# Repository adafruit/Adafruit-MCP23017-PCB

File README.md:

## Adafruit MCP23017 I2C GPIO Expander Breakout - STEMMA QT / QWIIC PCB

<a href="http://www.adafruit.com/products/5346"><br/>
Click here to purchase one from the Adafruit shop</a>

PCB files for the Adafruit MCP23017 I2C GPIO Expander Breakout - STEMMA QT / QWIIC. 

Format is EagleCAD schematic and board layout
* https://www.adafruit.com/product/5346

### Description

We’ve gotten a lot of requests for a MCP23017 breakout and we’ve always sorta been like “ehh why not just use the DIP chip?” but with STEMMA QT we could see the use case for a plug and play version that comes with all the passives on board. This Adafruit MCP23017 I2C GPIO Expander Breakout has 16 GPIO with matching ground pad.

We particularly like the '17 as an expander for it's simple no-nonsense capability. It runs happily from 3V or 5V logic and power. Each GPIO can be an output driving up to 25mA, so LEDs are no problem. Or, each can be an input, with optional pullup. There are two IRQ pins that are configurable for what inputs to keep track of so no I2C bus polling is required. With 3 address pins, you can have up to 8 on a single bus for a total of 8 x 16 = 128 GPIO all on one I2C bus!

We've got solid Arduino and CircuitPython libraries with examples, all ready for this chip. But even if you are using some other platform, the MCP23017 is so classic, you'll likely be able to find example code.

Comes with two sticks of header so you can use it in a breadboard, with some soldering. You can also free-wire buttons by connecting one side to the GPIO (set as input with pullup) and the other side to a ground pad.

To get you going fast, we spun up a custom-made PCB in the STEMMA QT form factor, making it easy to interface with. The STEMMA QT connectors on either side are compatible with the SparkFun Qwiic I2C connectors. This allows you to make solderless connections between your development board and the MCP23017 or to chain it with a wide range of other sensors and accessories using a compatible cable.

### License

Adafruit invests time and resources providing this open source design, please support Adafruit and open-source hardware by purchasing products from [Adafruit](https://www.adafruit.com)!

Designed by Limor Fried/Ladyada for Adafruit Industries.

Creative Commons Attribution/Share-Alike, all text above must be included in any redistribution. 
See license.txt for additional details.

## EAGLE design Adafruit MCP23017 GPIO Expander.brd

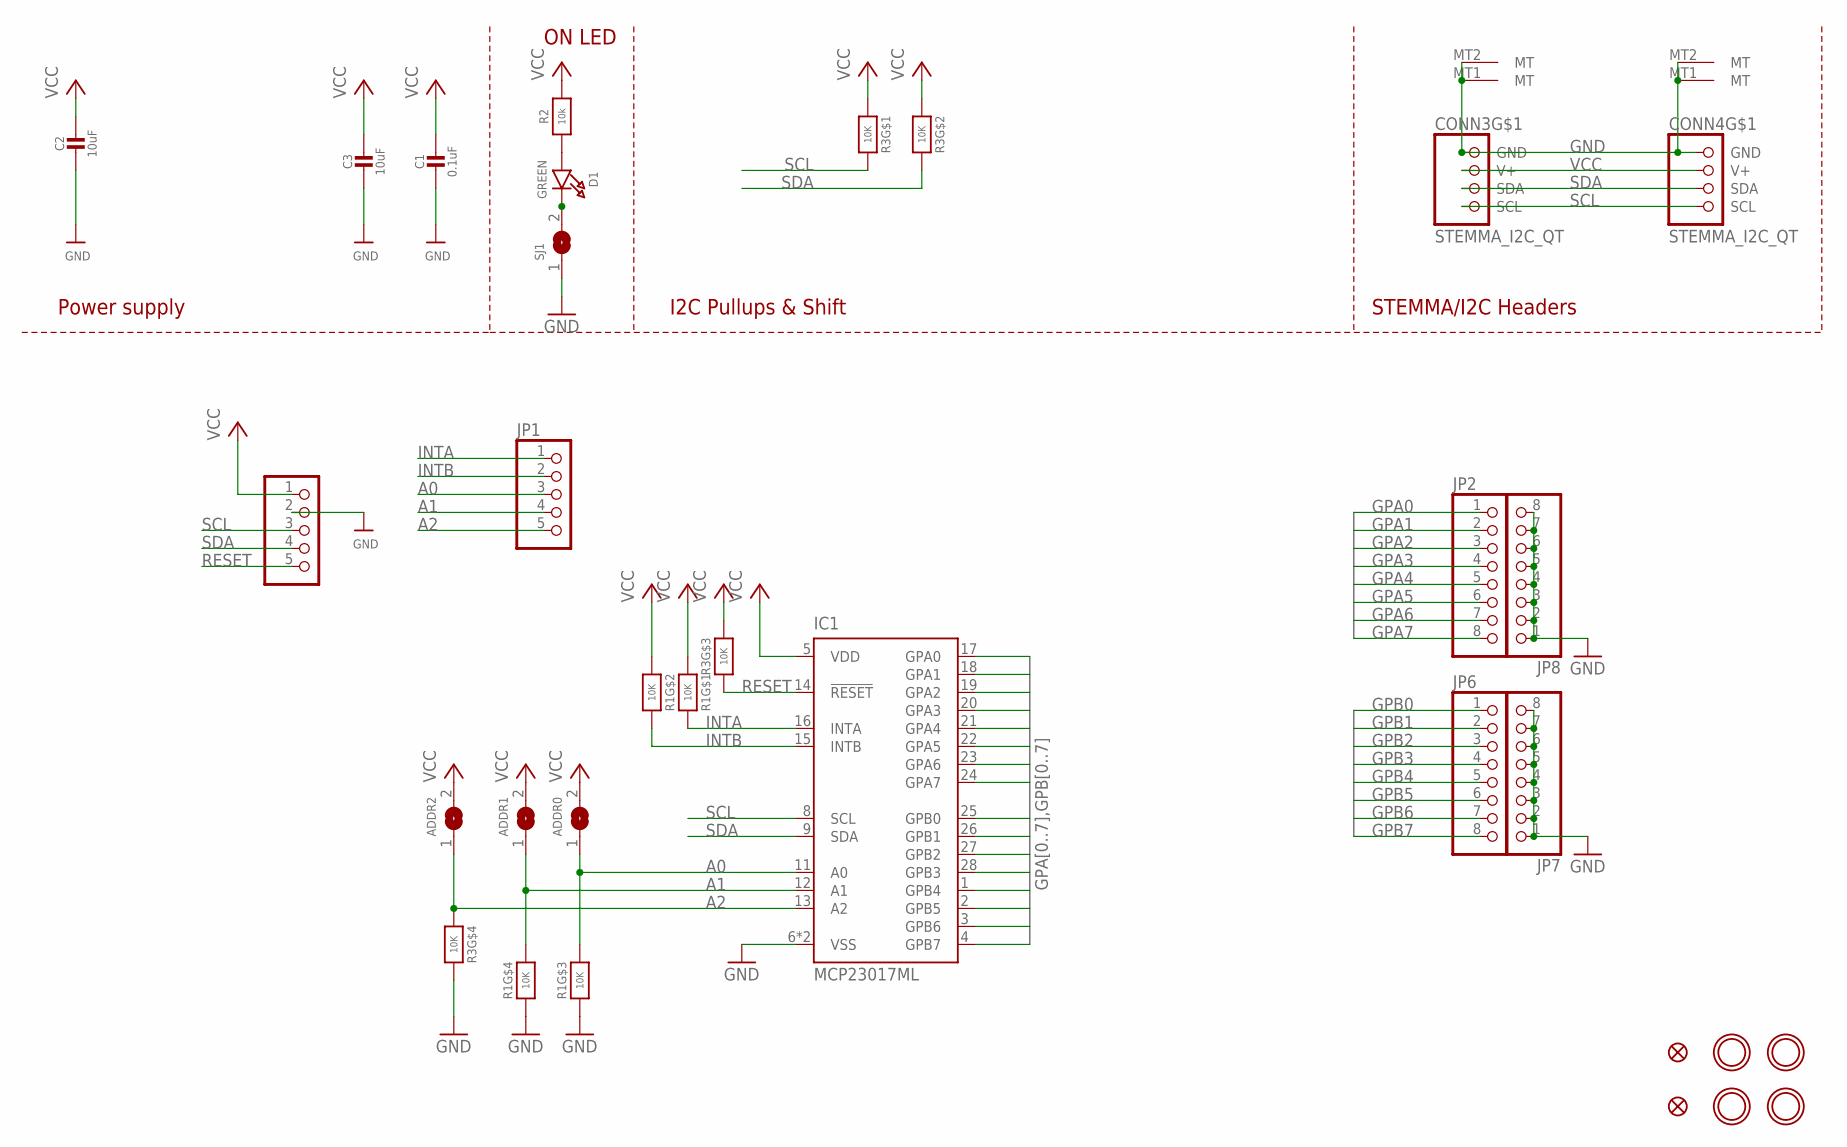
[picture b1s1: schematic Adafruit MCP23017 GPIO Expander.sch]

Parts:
ADDR0, ADDR1, ADDR2: SOLDERJUMPER; SOLDERJUMPER_ARROW_NOPASTE
C1: 0.1uF; 0603-NO
C2, C3: 10uF; 0805-NO
CONN3, CONN4: STEMMA_I2C_QT; JST_SH4
D1: GREEN; CHIPLED_0603_NOOUTLINE
FID3, FID4: FIDUCIAL_1MM
IC1: MCP23017ML; QFN28-ML_6X6MM
JP1, JP5: HEADER-1X570MIL; 1X05_ROUND_70
JP2, JP6, JP7, JP8: HEADER-1X870MIL; 1X08_ROUND_70
R1, R3: 10K; RESPACK_4X0603
R2: 10k; 0603-NO
SJ1: SOLDERJUMPERCLOSED; SOLDERJUMPER_CLOSEDWIRE
U$1, U$17, U$19, U$21: MOUNTINGHOLE2.5; MOUNTINGHOLE_2.5_PLATED

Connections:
A0: ADDR0.1, IC1.11 (A0), JP1.3, R1.6 (2)
A1: ADDR1.1, IC1.12 (A1), JP1.4, R1.5 (2)
A2: ADDR2.1, IC1.13 (A2), JP1.5, R3.4 (1)
GND: C1.2, C2.2, C3.2, CONN3.1 (GND), CONN3.MT1 (MT), CONN3.MT2 (MT), CONN4.1 (GND), CONN4.MT1 (MT), CONN4.MT2 (MT), IC1.6 (VSS), IC1.EXP (VSS), JP5.2, JP7.1, JP7.2, JP7.3, JP7.4, JP7.5, JP7.6, JP7.7, JP7.8, JP8.1, JP8.2, JP8.3, JP8.4, JP8.5, JP8.6, JP8.7, JP8.8, R1.3 (1), R1.4 (1), R3.5 (2), SJ1.1
GPA0: IC1.17 (GPA0), JP2.1
GPA1: IC1.18 (GPA1), JP2.2
GPA2: IC1.19 (GPA2), JP2.3
GPA3: IC1.20 (GPA3), JP2.4
GPA4: IC1.21 (GPA4), JP2.5
GPA5: IC1.22 (GPA5), JP2.6
GPA6: IC1.23 (GPA6), JP2.7
GPA7: IC1.24 (GPA7), JP2.8
GPB0: IC1.25 (GPB0), JP6.1
GPB1: IC1.26 (GPB1), JP6.2
GPB2: IC1.27 (GPB2), JP6.3
GPB3: IC1.28 (GPB3), JP6.4
GPB4: IC1.1 (GPB4), JP6.5
GPB5: IC1.2 (GPB5), JP6.6
GPB6: IC1.3 (GPB6), JP6.7
GPB7: IC1.4 (GPB7), JP6.8
INTA: IC1.16 (INTA), JP1.1, R1.8 (2)
INTB: IC1.15 (INTB), JP1.2, R1.7 (2)
unnamed: D1.A, R2.1
unnamed: D1.C, SJ1.2
RESET: IC1.14 (!RESET), JP5.5, R3.3 (1)
SCL: CONN3.4 (SCL), CONN4.4 (SCL), IC1.8 (SCL), JP5.3, R3.8 (2)
SDA: CONN3.3 (SDA), CONN4.3 (SDA), IC1.9 (SDA), JP5.4, R3.7 (2)
VCC: ADDR0.2, ADDR1.2, ADDR2.2, C1.1, C2.1, C3.1, CONN3.2 (V+), CONN4.2 (V+), IC1.5 (VDD), JP5.1, R1.1, R1.2 (1), R2.2, R3.1, R3.2 (1), R3.6 (2)

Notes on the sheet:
I2C Pullups & Shift
STEMMA/I2C Headers
ON LED
Power supply

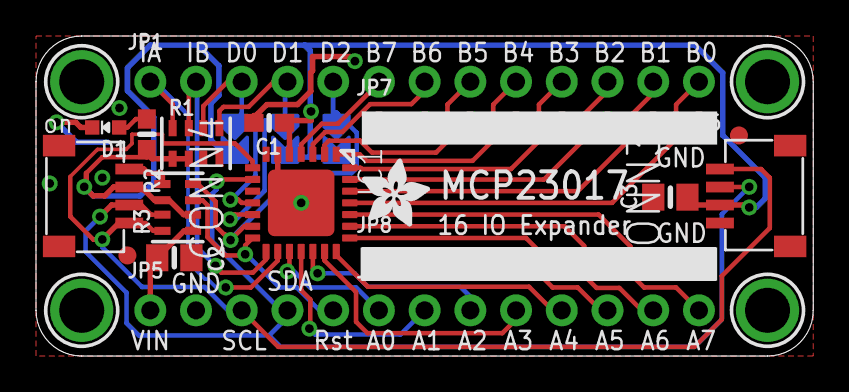
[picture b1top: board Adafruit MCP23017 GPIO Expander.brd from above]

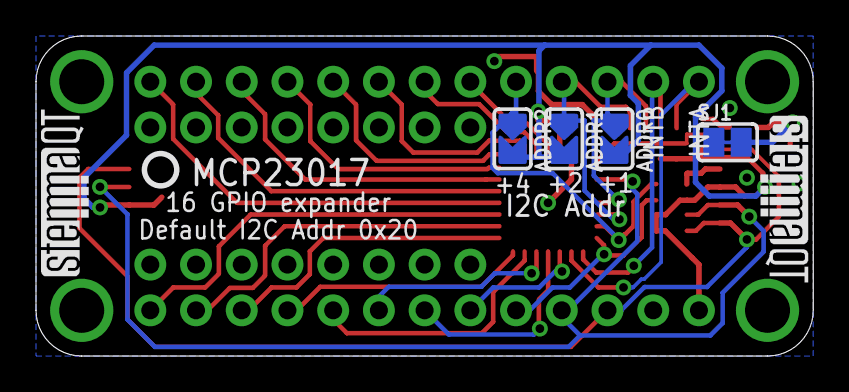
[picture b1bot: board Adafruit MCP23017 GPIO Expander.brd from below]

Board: 2 copper layers, 43.2 x 17.8 mm, 30 parts (7 on the bottom side), 28 nets.

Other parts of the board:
U$22: ADAFRUIT_3.5MM
U$25: PCBFEAT-REV-040
U$30, U$31: STEMMAQT

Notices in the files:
parts and their libraries:
microbuilder: This work is placed in the public domain, and may be freely used for commercial and non-commercial work with the following conditions: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
